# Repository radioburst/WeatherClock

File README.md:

# AVR Weather/Bitcoin Clock
A simple Clock with uses an ESP8266 to get Weather and Crypo currency information.

# Build
Build it using the 'avrgcc' and flash with 'avr dude'

# PCB
The PCB was designed with Kicad.

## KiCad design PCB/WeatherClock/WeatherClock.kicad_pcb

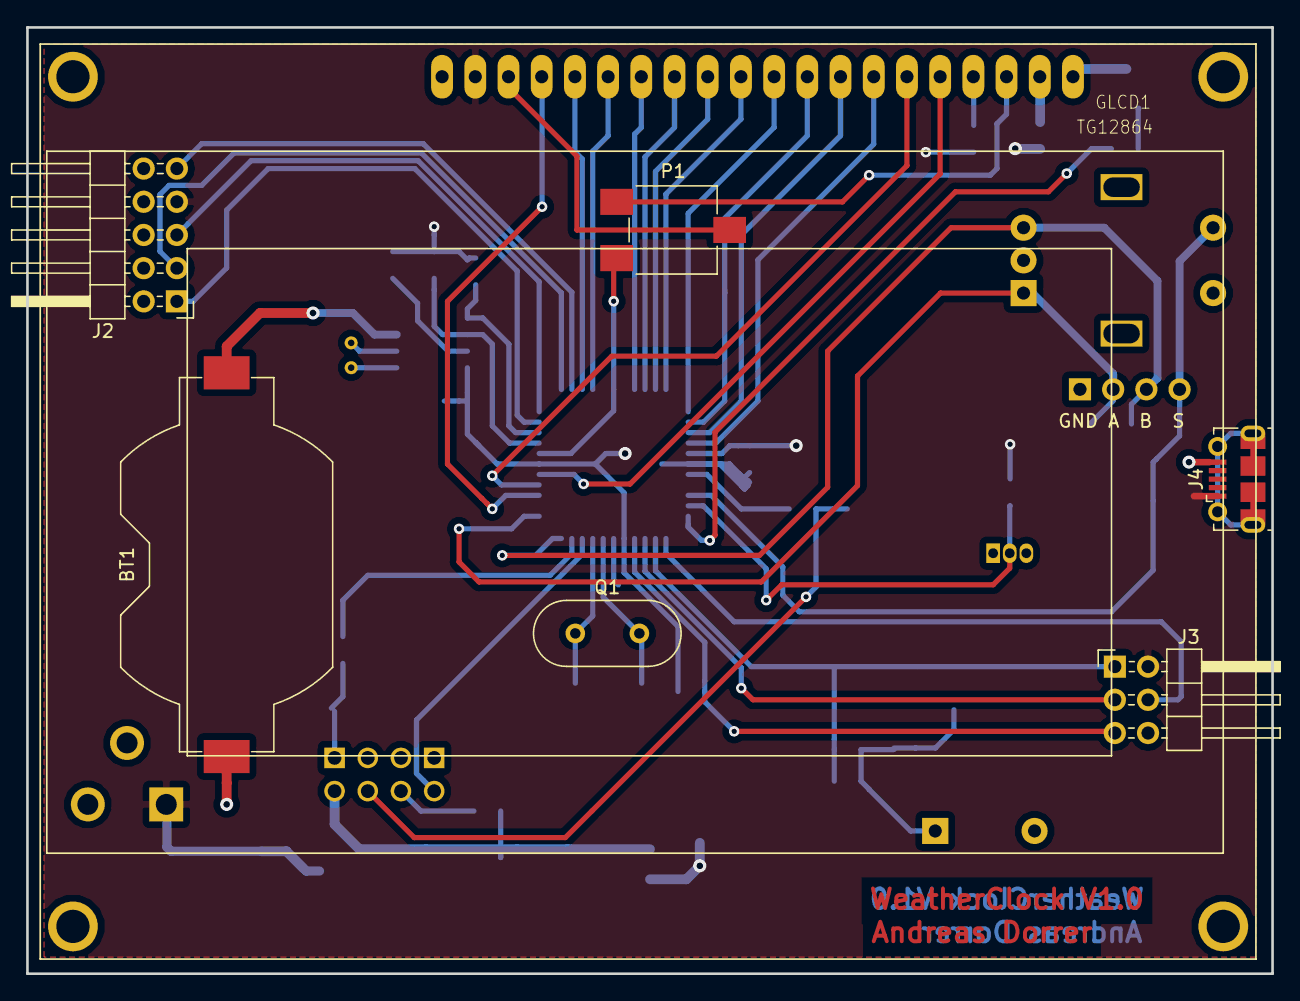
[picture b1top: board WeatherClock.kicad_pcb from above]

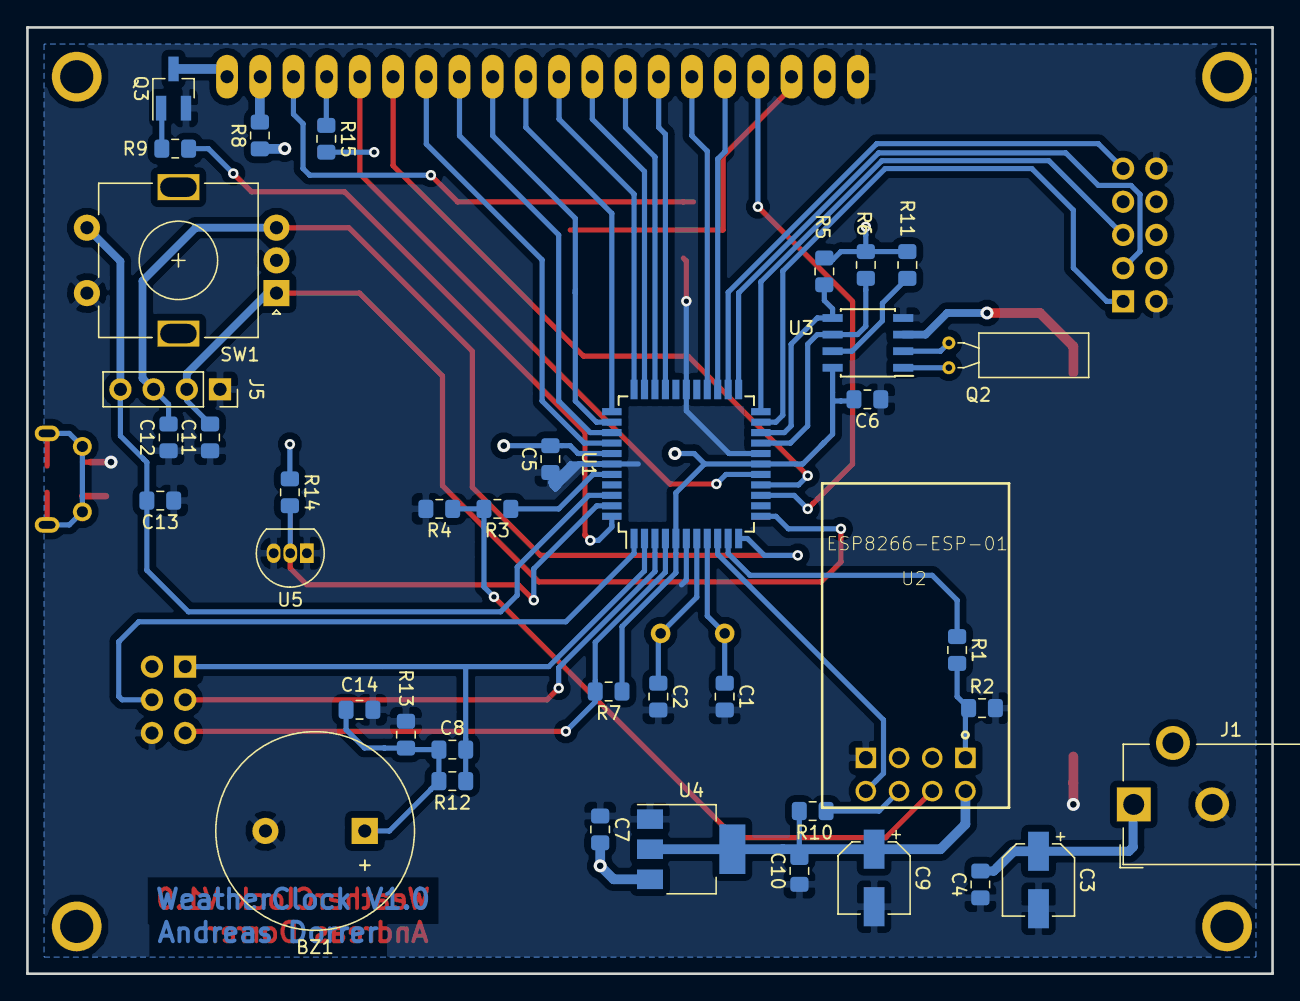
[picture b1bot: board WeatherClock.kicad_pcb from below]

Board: 2 copper layers, 95.3 x 72.4 mm, 47 parts (40 on the bottom side), 50 nets.

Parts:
BT1: Battery_Cell; BatteryHolder_Keystone_1058_1x2032
BZ1: Buzzer; Buzzer_15x7.5RM7.6
C1: 22pF; C_0805_2012Metric_Pad1.15x1.40mm_HandSolder
C2, C8, C14: 22pf; C_0805_2012Metric_Pad1.15x1.40mm_HandSolder
C3, C9: 47u; CP_Elec_5x5.8
C4, C5, C6, C7, C10, C11, C12, C13: 100nF; C_0805_2012Metric_Pad1.15x1.40mm_HandSolder
GLCD1: TG12864; GLCD_NEW
J1: Jack-DC; BarrelJack_CUI_PJ-102AH_Horizontal
J2: AVR-JTAG; PinHeader_2x05_P2.54mm_Horizontal
J3: AVR-ISP; PinHeader_2x03_P2.54mm_Horizontal
J4: USB_B_Micro; USB_Micro-B_Molex-105017-0001
J5: Conn_01x04_Male; PinSocket_1x04_P2.54mm_Vertical
P1: 100k; Potentiometer_ACP_CA6-VSMD_Vertical
Q1: 16MHz; Crystal_HC18-U_Vertical
Q2: 32.768kHz; Crystal_C38-LF_D3.0mm_L8.0mm_Horizontal
Q3: BC848; SOT-23_Handsoldering
R1, R3: 5k; R_0805_2012Metric_Pad1.15x1.40mm_HandSolder
R2, R4, R10: 10k; R_0805_2012Metric_Pad1.15x1.40mm_HandSolder
R5, R6, R11: 4.7k; R_0805_2012Metric_Pad1.15x1.40mm_HandSolder
R7, R15: 100k; R_0805_2012Metric_Pad1.15x1.40mm_HandSolder
R8: 220; R_0805_2012Metric_Pad1.15x1.40mm_HandSolder
R9: 1k; R_0805_2012Metric_Pad1.15x1.40mm_HandSolder
R12, R13: R; R_0805_2012Metric_Pad1.15x1.40mm_HandSolder
R14: 4k7; R_0805_2012Metric_Pad1.15x1.40mm_HandSolder
SW1: Rotary_Encoder_Switch; RotaryEncoder_Alps_EC11E-Switch_Vertical_H20mm
U1: ATmega644A-AU; TQFP-44_10x10mm_P0.8mm
U2: ESP8266-ESP-01; XCVR_ESP8266-01%2fESP-01
U3: DS1307+; SOIC-8_3.9x4.9mm_P1.27mm
U4: LM1117-3.3; SOT-223-3_TabPin2
U5: DS18S20; TO-92_Inline

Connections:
+3V3: C9.1, C10.2, R10.1, U2.8, U4.2
+5V: C3.1, C4.2, C5.2, C6.2, C7.2, GLCD1.P$2, J1.1, J2.7, J3.2, J4.1, R5.1, R6.1, R7.1, R8.1, R11.1, R14.1, R15.2, U1.5, U1.17, U1.38, U3.8, U4.3
+BATT: BT1.1, U3.3
CS1: GLCD1.P$15, U1.15
CS2: GLCD1.P$16, U1.16
GND: BT1.2, BZ1.2, C1.2, C2.2, C3.2, C4.1, C5.1, C6.1, C7.1, C9.2, C10.1, C11.1, C12.1, C13.1, C14.1, GLCD1.P$1, J1.2, J2.2, J2.10, J3.6, J4.5, J5.1, P1.1, Q3.2, R2.2, R4.2, R13.2, SW1.C, SW1.S2, U1.6, U1.18, U1.28, U1.39, U2.4, U3.4, U4.1, U5.1, U5.3
unnamed: BZ1.1, C8.1, C14.2, R12.2, R13.1
unnamed: C1.1, Q1.1, U1.8
unnamed: C2.1, Q1.2, U1.7
unnamed: C8.2, J3.1, R12.1, U1.2
unnamed: C11.2, J5.2, SW1.A, U1.12
unnamed: C12.2, J5.3, SW1.B, U1.11
unnamed: C13.2, J5.4, SW1.S1, U1.42
unnamed: GLCD1.P$3, P1.2
unnamed: GLCD1.P$4, U1.14
unnamed: GLCD1.P$5, U1.25
unnamed: GLCD1.P$6, U1.26
unnamed: GLCD1.P$7, U1.30
unnamed: GLCD1.P$8, U1.31
unnamed: GLCD1.P$9, U1.32
unnamed: GLCD1.P$10, U1.33
unnamed: GLCD1.P$11, U1.34
unnamed: GLCD1.P$12, U1.35
unnamed: GLCD1.P$13, U1.36
unnamed: GLCD1.P$14, U1.37
unnamed: GLCD1.P$17, R15.1
unnamed: GLCD1.P$18, P1.3
unnamed: GLCD1.P$19, R8.2
unnamed: GLCD1.P$20, Q3.3
unnamed: J2.1, U1.21
unnamed: J2.3, U1.23
unnamed: J2.5, U1.22
unnamed: J2.9, U1.24
unnamed: J3.3, U1.3
unnamed: J3.4, U1.1
unnamed: J3.5, R7.2, U1.4
unnamed: Q2.1, U3.1
unnamed: Q2.2, U3.2
unnamed: Q3.1, R9.1
unnamed: R1.1, U1.10
unnamed: R1.2, R2.1, U2.1
unnamed: R3.1, U1.40
unnamed: R3.2, R4.1, U2.7
unnamed: R5.2, U1.20, U3.5
unnamed: R6.2, U1.19, U3.6
unnamed: R9.2, U1.44
unnamed: R10.2, U2.6
unnamed: R11.2, U3.7
unnamed: R14.2, U1.43, U5.2
unnamed: U1.9, U2.5

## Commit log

2024-04-23 init project
2024-04-24 add readme
